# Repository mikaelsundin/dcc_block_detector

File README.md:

# dcc_block_detector
A dcc block detector based on STM32F030 and measure current over diode-drop

#This detector is usefull both for N-Scale and H0-scale. 
A SMC diode of 5A can handle alot of current.
For N-scale its possible to use regular pin header at IO1, IO2 (max 3A).
For HO scale i recommend screw terminal to handle more current.

#Note
Another board with a MCU is needed to translate from uart to other protocols.

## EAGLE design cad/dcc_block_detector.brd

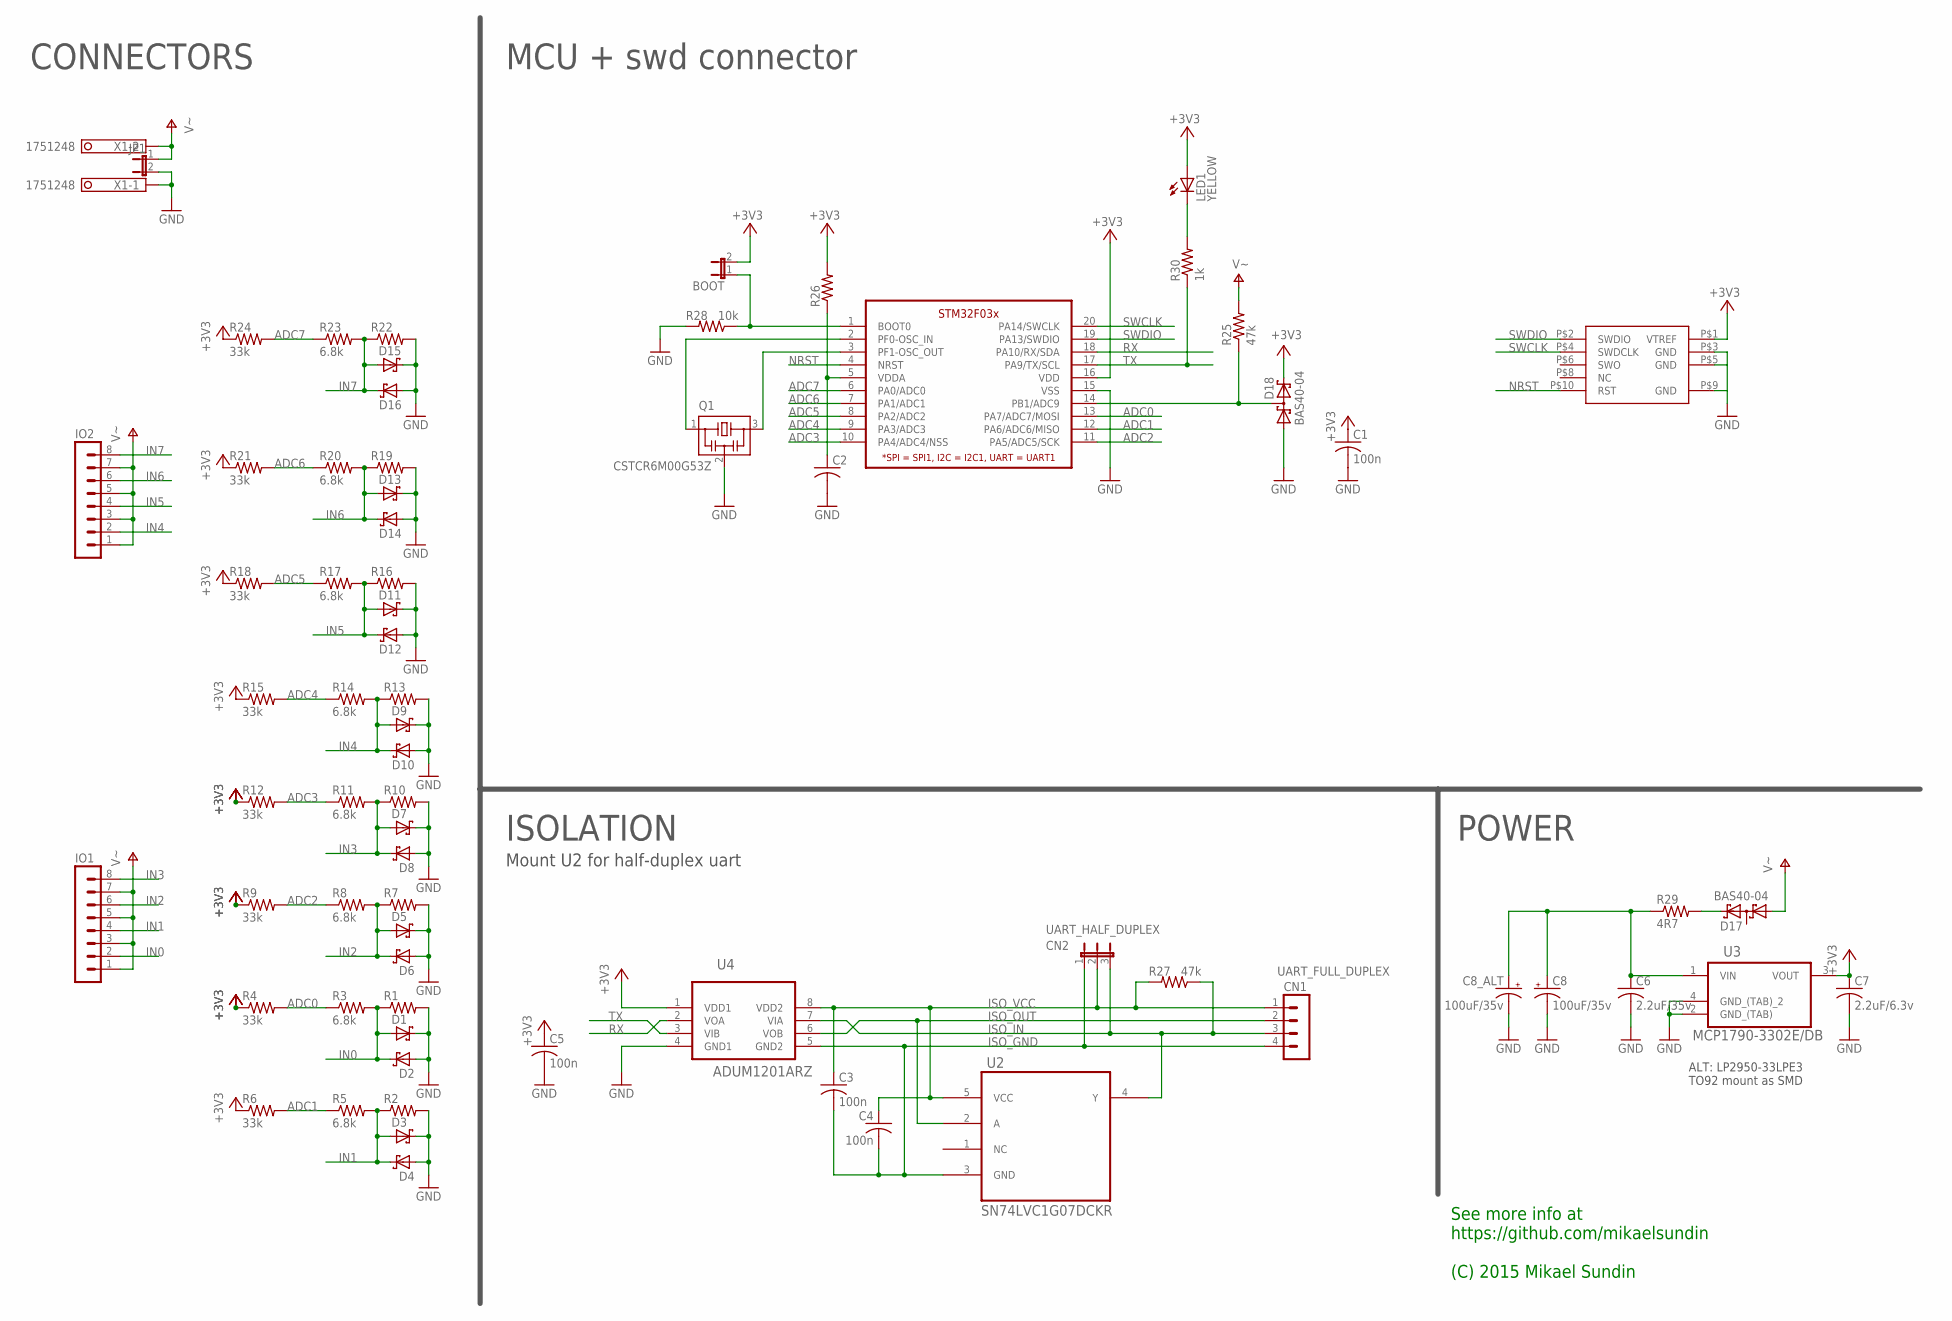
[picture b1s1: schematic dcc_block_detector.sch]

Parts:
BOOT: JP1E; JP1
C1, C3, C4, C5: 100n; C0603
C2: C-USC0603; C0603
C6: 2.2uF/35v; C0805
C7: 2.2uF/6.3v; C0805
C8: 100uF/35v; UD-6,3X7,7_NICHICON
C8_ALT: 100uF/35v; E2,5-6
CN1: UART_FULL_DUPLEX; MA04-1
CN2: UART_HALF_DUPLEX; JP2
D1, D2, D3, D4, D5, D6, D7, D8, D9, D10, D11, D12, D13, D14, D15, D16: SCHOTTKY-DIODESMC; SMC
D17, D18: BAS40-04; SOT23
IO1, IO2: MA08-1W
JP1: JP1E; JP1
LED1: YELLOW; CHIPLED_0603
Q1: CSTCR6M00G53Z; CSTER12M
R1, R2, R7, R10, R13, R16, R19, R22: R-US_R1206; R1206
R3, R5, R8, R11, R14, R17, R20, R23: 6.8k; R0603
R4, R6, R9, R12, R15, R18, R21, R24: 33k; R0603
R25, R27: 47k; R0603
R26: R-US_R0603; R0603
R28: 10k; R0603
R29: 4R7; R1206
R30: 1k; R0603
U2: SN74LVC1G07DCKR; SOT65P210X110-5N
U3: MCP1790-3302E/DB; SOT230P700X180-4N
U4: ADUM1201ARZ; SOIC127P600X175-8N
U$1: STM32F03X_TSSOP20
U$2: SWD; ARM_SWD_2X5
X1: 1751248

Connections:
+3V3: BOOT.2, C1.1, C5.1, C7.1, D18.2 (C2), LED1.A, R4.1, R6.1, R9.1, R12.1, R15.1, R18.1, R21.1, R24.1, R26.2, U3.3 (VOUT), U4.1 (VDD1), U$1.16 (VDD), U$2.P$1 (VTREF)
ADC0: R3.1, R4.2, U$1.13 (PA7/ADC7/MOSI)
ADC1: R5.1, R6.2, U$1.12 (PA6/ADC6/MISO)
ADC2: R8.1, R9.2, U$1.11 (PA5/ADC5/SCK)
ADC3: R11.1, R12.2, U$1.10 (PA4/ADC4/NSS)
ADC4: R14.1, R15.2, U$1.9 (PA3/ADC3)
ADC5: R17.1, R18.2, U$1.8 (PA2/ADC2)
ADC6: R20.1, R21.2, U$1.7 (PA1/ADC1)
ADC7: R23.1, R24.2, U$1.6 (PA0/ADC0)
GND: C1.2, C2.2, C5.2, C6.2, C7.2, C8.-, C8_ALT.-, D1.C, D2.A, D3.C, D4.A, D5.C, D6.A, D7.C, D8.A, D9.C, D10.A, D11.C, D12.A, D13.C, D14.A, D15.C, D16.A, D18.1 (A1), JP1.2, Q1.2, R1.2, R2.2, R7.2, R10.2, R13.2, R16.2, R19.2, R22.2, R28.2, U3.2 (GND_(TAB)), U3.4 (GND_(TAB)_2), U4.4 (GND1), U$1.15 (VSS), U$2.P$3 (GND), U$2.P$5 (GND), U$2.P$9 (GND), X1.1
IN0: D1.A, D2.C, IO1.2, R1.1, R3.2
IN1: D3.A, D4.C, IO1.4, R2.1, R5.2
IN2: D5.A, D6.C, IO1.6, R7.1, R8.2
IN3: D7.A, D8.C, IO1.8, R10.1, R11.2
IN4: D9.A, D10.C, IO2.2, R13.1, R14.2
IN5: D11.A, D12.C, IO2.4, R16.1, R17.2
IN6: D13.A, D14.C, IO2.6, R19.1, R20.2
IN7: D15.A, D16.C, IO2.8, R22.1, R23.2
ISO_GND: C3.2, C4.2, CN1.4, CN2.1, U2.3 (GND), U4.5 (GND2)
ISO_IN: CN1.3, CN2.3, R27.1, U2.4 (Y), U4.7 (VIA)
ISO_OUT: CN1.2, U2.2 (A), U4.6 (VOB)
ISO_VCC: C3.1, C4.1, CN1.1, CN2.2, R27.2, U2.5 (VCC), U4.8 (VDD2)
unnamed: D18.3 (C1A2), R25.1, U$1.14 (PB1/ADC9)
unnamed: C2.1, R26.1, U$1.5 (VDDA)
unnamed: D17.2 (C2), R29.2
unnamed: Q1.1, U$1.2 (PF0-OSC_IN)
unnamed: Q1.3, U$1.3 (PF1-OSC_OUT)
unnamed: BOOT.1, R28.1, U$1.1 (BOOT0)
unnamed: C6.1, C8.+, C8_ALT.+, R29.1, U3.1 (VIN)
unnamed: LED1.C, R30.2
NRST: U$1.4 (NRST), U$2.P$10 (RST)
RX: U4.2 (VOA), U$1.18 (PA10/RX/SDA)
SWCLK: U$1.20 (PA14/SWCLK), U$2.P$4 (SWDCLK)
SWDIO: U$1.19 (PA13/SWDIO), U$2.P$2 (SWDIO)
TX: R30.1, U4.3 (VIB), U$1.17 (PA9/TX/SCL)
V+: D17.1 (A1), IO1.1, IO1.3, IO1.5, IO1.7, IO2.1, IO2.3, IO2.5, IO2.7, JP1.1, R25.2, X1.2

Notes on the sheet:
CONNECTORS
MCU + swd connector
ISOLATION
POWER
See more info at https://github.com/mikaelsundin (C) 2015 Mikael Sundin
Mount U2 for half-duplex uart
ALT: LP2950-33LPE3 TO92 mount as SMD

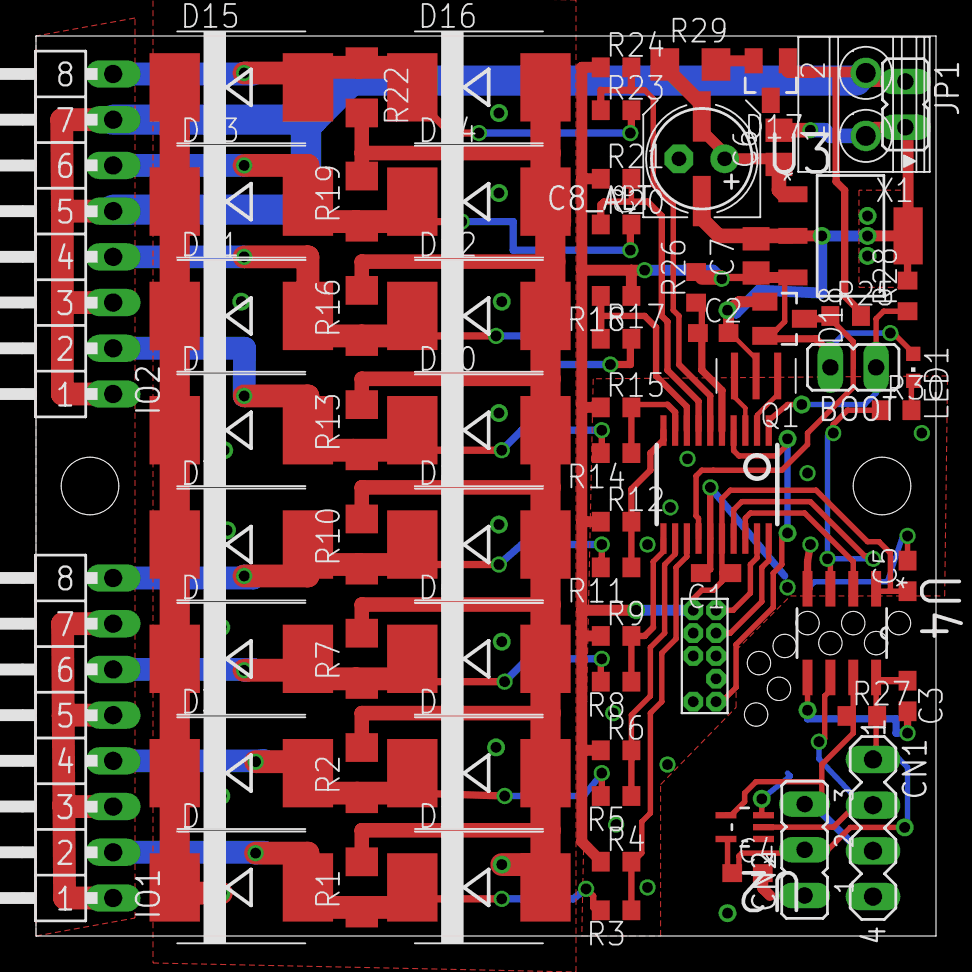
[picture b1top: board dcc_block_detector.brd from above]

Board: 2 copper layers, 50.0 x 50.0 mm, 71 parts (0 on the bottom side), 36 nets.

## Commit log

2015-10-08 Added cad files and code that perform some basic tasks.
2015-10-08 Update README.md
    fixed typo
2015-10-23 Code working as expected. First working release.
2015-10-24 Lower clock speed to save power. Added a image of a soldered board.
2019-02-15 Update README.md
    Fixed typho
